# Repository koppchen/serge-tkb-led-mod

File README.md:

# Serge TKB LED Mod

Small PCB designed to add row indicator LEDs to the Serge TKB (Touch Activated Keyboard Sequencer).  This was designed for The Human Comparator TKB version, which was based on the original Serge TKB schematics.

This repo contains the EAGLE board and schematic files, along with the LTSpice schematic for circuit simulation.

## LED mod PCB 

The LED Mod PCB is small enough to be mounted on the top right corner of the main PCB.

Pads labeled **GND**, **VCC**, **A**, & **B** are wired to the bottom of CD4520BE on the main PCB.  Pads labeled **1**, **2**, **3**, & **4** are wired to the LEDs of sequencer rows A (1), B (2), C (3), and D (4).

Wiring the CD4520BE pins to the LED mod PCB.

### Mounted mod PCB

Two nuts will give enough space between the main PCB and mod PCB for the wires.

### LED wiring

LED anodes are wired to the mod PCB pads **1**-**4**.  LED cathodes are wired to ground.

## BOM

| Value   | QTY | Description | Mouser Part # |
|:--------|:---:|:------------|:--------------|
| CD4051BE | 1 | CMOS Single 8-Channel Analog Multiplexer/Demultiplexer with Logic-Level Conversion | [595-CD4051BE][cd4051] |
| R1 | 1 | 4.99k Resistor |  |
| R2 | 1 | 1.2k Resistor |  |
|  | 4 | Standard LEDs - 3mm Red 25mcd 640nm 40 deg Diffused | [604-WP710A10LSRD][red-leds] |
|  | 4 | LED Lenses Red Fresnel 3mm Lens  | [593-1700R][red-led-lenes] |

[cd4051]: https://www.mouser.com/ProductDetail/595-CD4051BE
[red-leds]: https://www.mouser.com/ProductDetail/604-WP710A10LSRD
[red-led-lenes]: https://www.mouser.com/ProductDetail/593-1700R

## Resources

Serge TKB Schematics:  
<http://machines.hyperreal.org/manufacturers/Serge/schematics/>

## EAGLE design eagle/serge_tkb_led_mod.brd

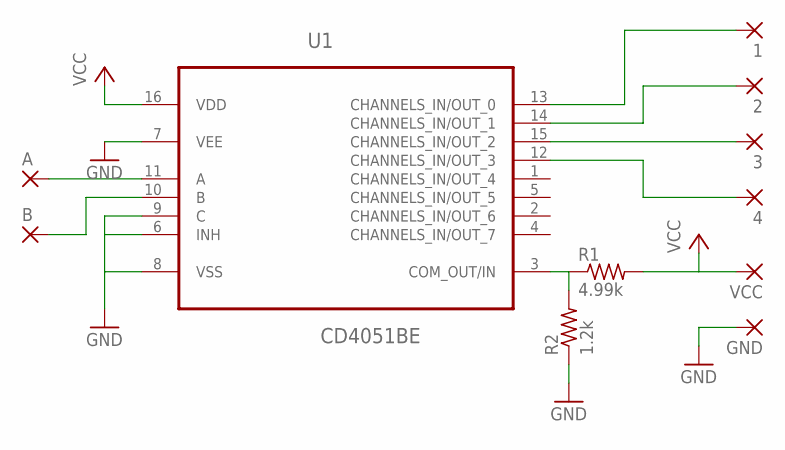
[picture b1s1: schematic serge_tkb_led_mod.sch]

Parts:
1, 2, 3, 4: 3,17/1,3
A: 3,17/1,3
B: 3,17/1,3
GND: 3,17/1,3
R1: 4.99k; 0207/10
R2: 1.2k; 0207/10
U1: CD4051BE; DIP254P762X508-16
VCC: 3,17/1,3

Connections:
A: A.1, U1.11 (A)
GND: GND.1, R2.1, U1.6 (INH), U1.7 (VEE), U1.8 (VSS), U1.9 (C)
unnamed: R1.1, R2.2, U1.3 (COM_OUT/IN)
unnamed: 1.1, U1.13 (CHANNELS_IN/OUT_0)
unnamed: 2.1, U1.14 (CHANNELS_IN/OUT_1)
unnamed: 3.1, U1.15 (CHANNELS_IN/OUT_2)
unnamed: 4.1, U1.12 (CHANNELS_IN/OUT_3)
unnamed: B.1, U1.10 (B)
VCC: R1.2, U1.16 (VDD), VCC.1

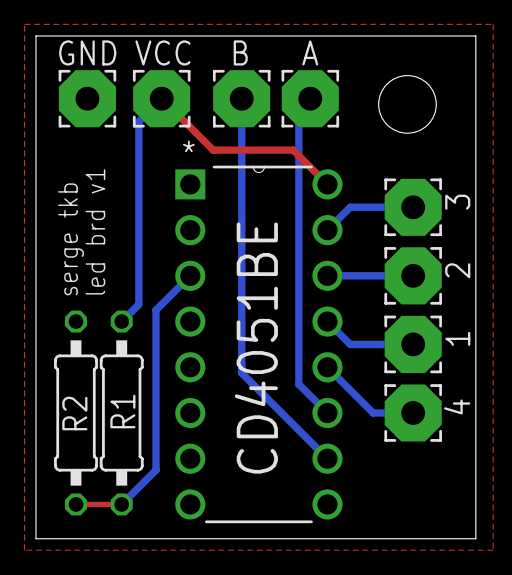
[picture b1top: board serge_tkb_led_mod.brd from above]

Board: 2 copper layers, 24.4 x 27.9 mm, 11 parts (0 on the bottom side), 9 nets.

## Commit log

2018-04-17 Add EAGLE and LTSpice files along with documentation
